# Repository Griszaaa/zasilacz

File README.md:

# Zasilacz stabilizowany regulowany

## Założenia projektowe
Założeniem projektu było skonstruowanie kompletnego dwukanałowego zasilacza stabilizowanego z płynną regulacją napięcia wyjściowego od 1.25 V do 12 V. Sprzętową realizację idei zasilacza oparto o scalony układ stabilizatora liniowego LM317. Z uwagi na dużą wydajność prądową stabilizatora należało uwzględnić rozproszenie wydzielającego się na nim ciepła. Zasilacz domyślnie powinien być wyposażony w potencjometryczną regulację napięcia wraz z jego graficzną reprezentacją na wyświetlaczu 7–segmentowym dołączonego miernika panelowego, a ponadto w rejestrację rzeczywistego poboru prądu przez obciążenie. Wyjście zasilacza przewidziano jako gniazda DC 2.1/5.5.
## Realizacja
Prace projektowe rozpoczęto od stworzenia schematu urządzenia wyłączając z niego transformator, jako element nienależący do zasadniczej części zasilacza. Na podstawie schematu zaprojektowano, a następnie samodzielnie wykonano płytkę PCB (metoda termotransferu), dla obu kanałów zasilacza. Do modułów dołączono zakupione wcześniej
mierniki panelowe oraz gniazda DC. Do wejścia podłączono transformator toroidalny o dwóch uzwojeniach wtórnych (2x15V; 1,67 A; 50VA). W trakcie jego zakupu musiano dobrać odpowiednio jego moc, tak, aby jako blok przed zasilaczem nie ograniczał jego możliwości dotyczących uzyskiwanej mocy. Jako chłodzenie pasywne zastosowano dwa płaskie radiatory przykręcone do obudowy LM317. W trakcie realizacji projektu zdecydowano się na dodanie do obwodu uzwojenia pierwotnego transformatora wyłącznika oraz bezpiecznika dla usprawnienia działania oraz poprawy bezpieczeństwa korzystania z urządzenia.
## Zasada działania
Zasilacz wykorzystuje działanie układu LM317, który pozwala za pomocą dzielnika rezystancyjnego dostrojenie napięcia wyjściowego. Dzięki zastosowaniu potencjometru regulacja ta odbywa się płynnie. Urządzenie jest podłączane do sieci 230 V następnie transformator obniża jego napięcie do 15 V RMS. Dalej jest ono „prostowane” oraz filtrowane i przekazywane do wejścia stabilizatora, który odpowiednią jego część przesyła na swoje wyjście tym samym na wyjście zasilacza. Minimalna wartość napięcia wyjściowego wynosi około 1,25 V. Związane jest to z napięciem dropout występującym jako spadek napięcia na stabilizatorze, niezbędnym do jego prawidłowej pracy. Górna granica napięcia jest różna dla obu kanałów: dla zielonego wynosi około 19 V natomiast dla czerwonego około 16 V. Maksymalny prąd wyjściowy zasilacza to około 1.5 A, jednak zgodnie z notą aplikacyjną stabilizatora jest on możliwy do uzyskania tylko jeżeli różnica napięć między wejściem a wyjściem układu jest mniejsza lub równa 15 V, czyli, gdy napięcie wyjściowe zasilacza jest większe niż około 5 V. W przeciwnym przypadku prąd maksymalny wynosi 400 mA.
## Zgodność z założeniami
Niestety ze względu na niedopatrzenie produkcyjne mierników panelowych tj. brak wlutowanego bocznika, nie udało się wykonać rejestracji pobieranego przez obciążenie zasilacza prądu. Nie spełniono również pierwotnego zakresu regulacji napięcia. Założenie w trakcie powstawania projektu uległo zmianie, z uwagi na wykorzystanie transformatora umożliwiającego uzyskanie wyższego napięcia wyjściowego. Zakresy napięcia są różne dla obu kanałów z uwagi na różnice konstrukcyjne poszczególnych elementów całego układu.

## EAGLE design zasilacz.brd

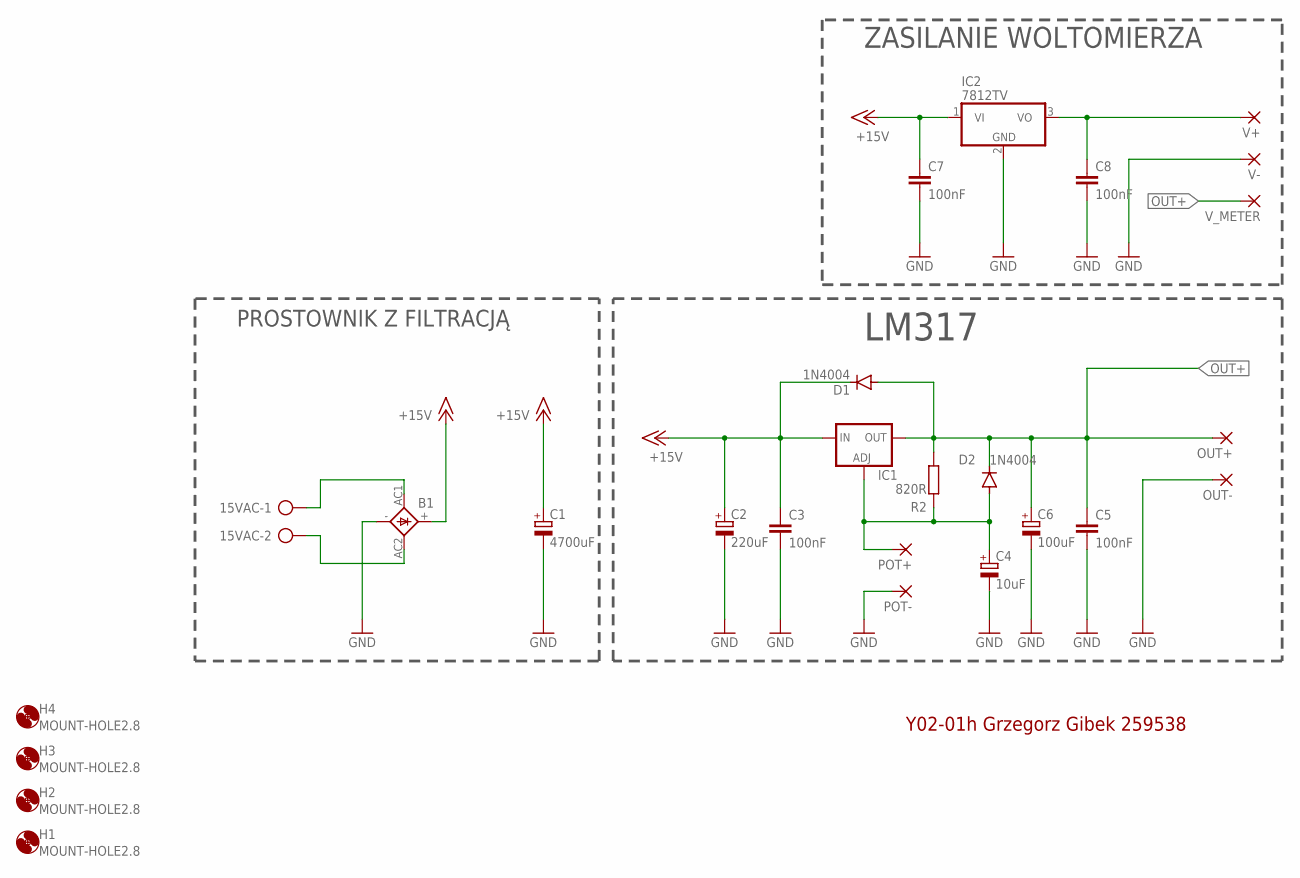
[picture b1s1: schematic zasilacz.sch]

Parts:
15VAC: AK500/2
B1: 2KBP
C1: 4700uF; E7,5-18
C2: 220uF; E5-10,5
C3, C5, C7, C8: 100nF; C050-025X075
C4: 10uF; E2,5-6E
C6: 100uF; E5-10,5
D1, D2: 1N4004; DO41-10
H1, H2, H3, H4: MOUNT-HOLE2.8; 2,8
IC1: LM317TS; 317TS
IC2: 7812TV; TO220V
OUT+: 3,81/1,4
OUT-: 3,81/1,4
POT+: 3,81/1,4
POT-: 3,81/1,4
R2: 820R; 0204/7
V+: 3,81/1,4
V-: 3,81/1,4
V_METER: 3,81/1,4

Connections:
+15V: B1.+, C1.+, C2.+, C3.1, C7.1, D1.C, IC1.3 (IN), IC2.1 (VI)
ADJ: C4.+, D2.A, IC1.1 (ADJ), POT+.1, R2.1
GND: B1.-, C1.-, C2.-, C3.2, C4.-, C5.2, C6.-, C7.2, C8.2, IC2.2 (GND), OUT-.1, POT-.1, V-.1
unnamed: 15VAC.1, B1.AC1
unnamed: 15VAC.2, B1.AC2
OUT+: C5.1, C6.+, D1.A, D2.C, IC1.2 (OUT), OUT+.1, R2.2, V_METER.1
V_ZAS: C8.1, IC2.3 (VO), V+.1

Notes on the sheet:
PROSTOWNIK Z FILTRACJĄ
LM317
Y02-01h Grzegorz Gibek 259538
ZASILANIE WOLTOMIERZA

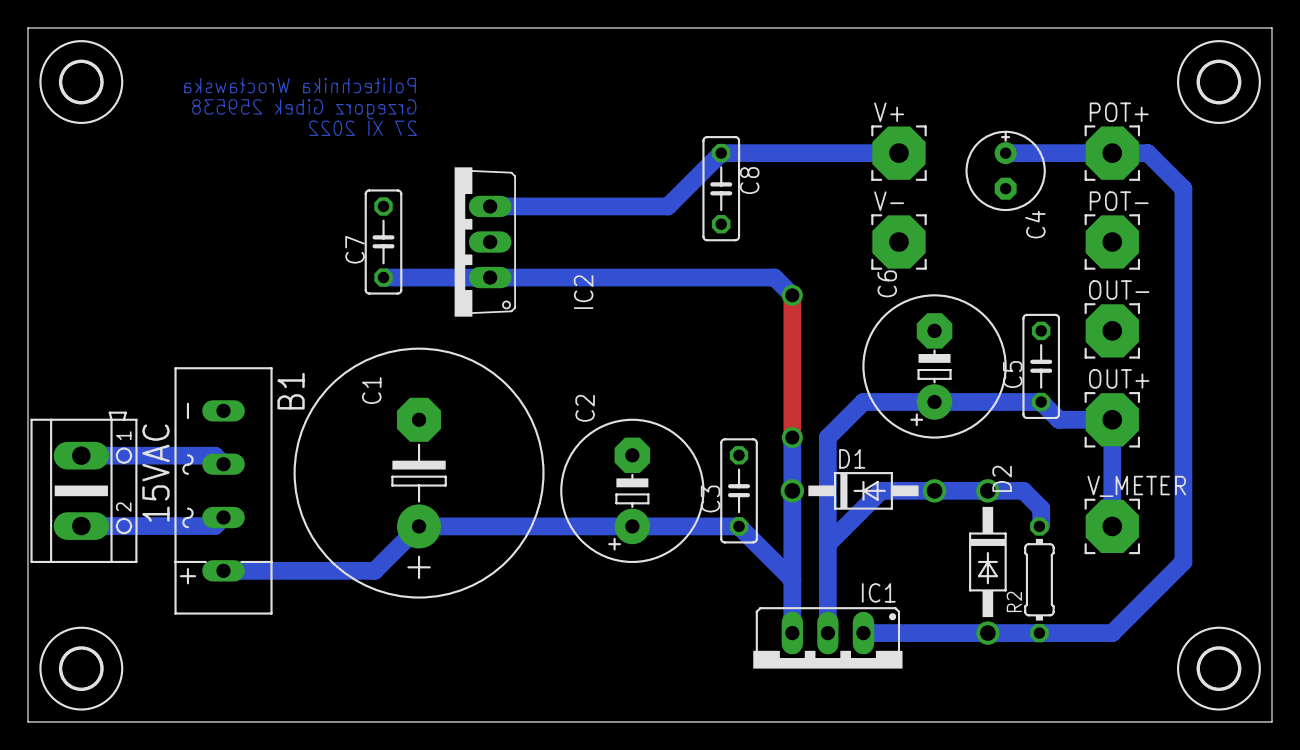
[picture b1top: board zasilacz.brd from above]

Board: 2 copper layers, 88.9 x 49.6 mm, 26 parts (0 on the bottom side), 7 nets.

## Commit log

2023-04-12 Dodanie plików projektu
2023-04-12 Dodanie wartości potencjometru
2023-04-12 Zdjęcie zasilacza
2025-07-24 Added photos
2025-07-24 deleting one photo
